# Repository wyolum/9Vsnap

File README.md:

# 9Vsnap
snaps in to 9V battery and provides 3V3 or 5V0 output

forked from snapVCC [https://hackaday.io/project/6269-snapvcc] by [Mahesh Venkitachalam] https://hackaday.io/electronut. This version attempts to make the size of the PCB match the cross-section of the battery. I also want to use is as a demo project while doing KiCad 101

License
-------
[CERN Open Hardware Licence v1.2 ]

[CERN Open Hardware Licence v1.2 ]:http://www.ohwr.org/attachments/2388/cern_ohl_v_1_2.txt

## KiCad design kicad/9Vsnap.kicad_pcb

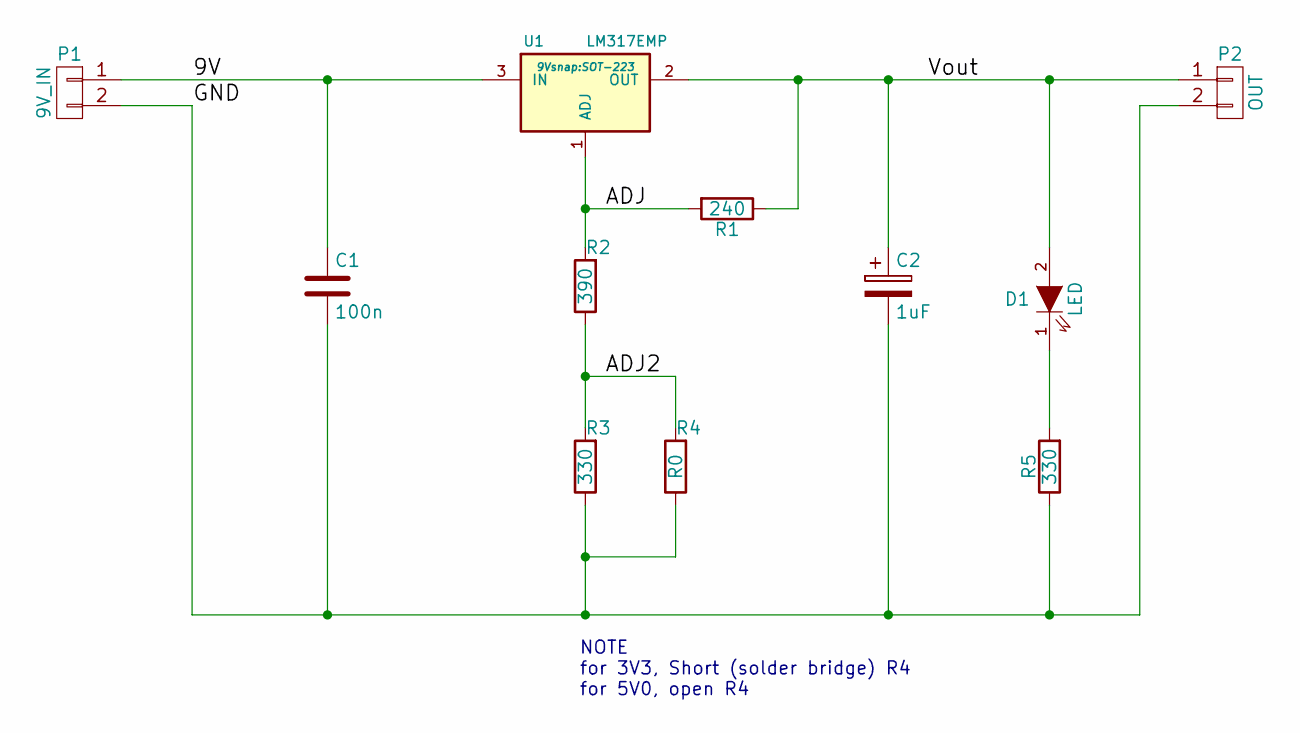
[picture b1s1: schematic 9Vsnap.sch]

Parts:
C1: 100n; C_0805_HandSoldering
C2: 1uF; C_0805_HandSoldering
D1: LED; LED-0805
P1: 9V_IN; 9V_clip
P2: OUT; Pin_Header_Straight_1x02
R1: 240; R_0805_HandSoldering
R2: 390; R_0805_HandSoldering
R3, R5: 330; R_0805_HandSoldering
R4: R0; R_0805_HandSoldering
U1: LM317EMP; SOT-223

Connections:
/9V: C1.1, P1.1, U1.3 (IN)
/ADJ: R1.2, R2.2, U1.1 (ADJ)
/ADJ2: R2.1, R3.2, R4.2
/GND: C1.2, C2.2, P1.2, P2.2, R3.1, R4.1, R5.1
/Vout: C2.1, D1.2 (A), P2.1, R1.1, U1.2 (OUT)
unnamed: D1.1 (K), R5.2

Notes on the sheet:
NOTE for 3V3, Short (solder bridge) R4 for 5V0, open R4

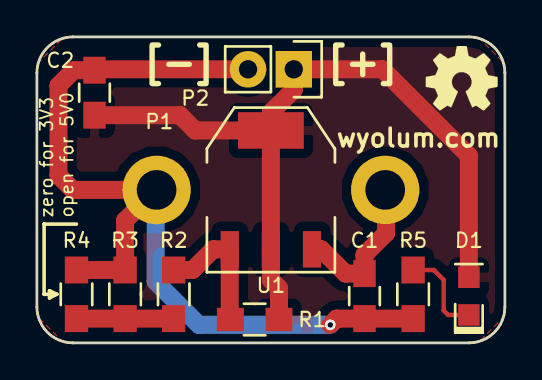
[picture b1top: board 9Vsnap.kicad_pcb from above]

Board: 2 copper layers, 26.0 x 17.0 mm, 11 parts (0 on the bottom side), 6 nets.

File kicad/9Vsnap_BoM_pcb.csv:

"Id";"Designator";"Package";"Quantity";"Designation";"Supplier and ref";
1;"G***,G***";"OSHW_logo_notext";2;"LOGO";;;
2;"P2";"Pin_Header_Straight_1x02";1;"OUT";;;
3;"U1";"SOT-223";1;"LM317EMP";;;
4;"R5,R3";"R_0805_HandSoldering";2;"330";;;
5;"R4";"R_0805_HandSoldering";1;"R0";;;
6;"R2";"R_0805_HandSoldering";1;"390";;;
7;"R1";"R_0805_HandSoldering";1;"240";;;
8;"D1";"LED-0805";1;"LED";;;
9;"C2";"C_0805_HandSoldering";1;"1uF";;;
10;"C1";"C_0805_HandSoldering";1;"100n";;;
11;"P1";"9V_clip_968";1;"9V_IN";;;

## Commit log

2015-06-15 looks done but need to verify
2015-06-16 Done. Gerbers ready
2015-06-18 increased radius of board corners
